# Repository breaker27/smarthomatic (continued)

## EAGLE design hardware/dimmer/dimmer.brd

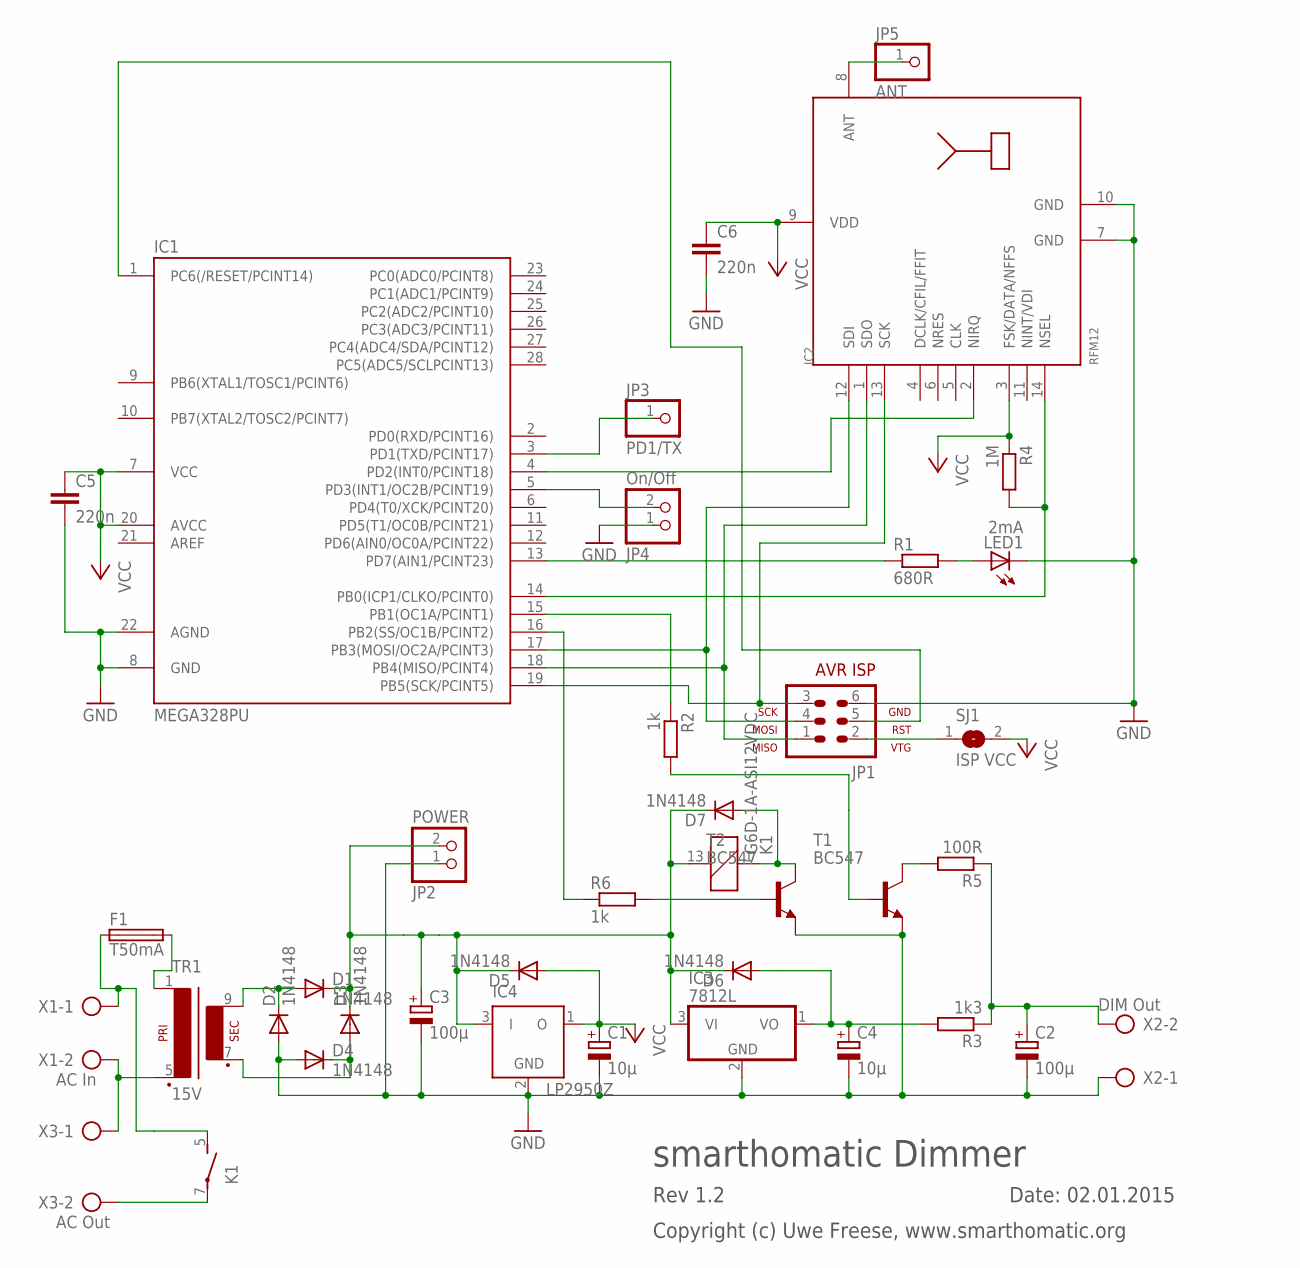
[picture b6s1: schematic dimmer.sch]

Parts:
C1, C4: 10µ; E1,8-4
C2, C3: 100µ; E1,8-4
C5, C6: 220n; C2.5-3
D1, D2, D3, D4, D5, D6, D7: 1N4148; DO35-7
F1: T50mA; SH22,5
IC1: MEGA328PU; DIL28-3
IC2: RFM12; RFM
IC3: 7812L; TO92
IC4: LP2950Z; TO92
JP1: AVR-ISP-6
JP2: POWER; 1X02
JP3: PD1/TX; 1X01
JP4: On/Off; 1X02
JP5: ANT; 1X01
K1: G6D-1A-ASI12VDC; G6D
LED1: 2mA; LED3MM
R1: 680R; 0207/7
R2, R6: 1k; 0207/7
R3: 1k3; 0207/7
R4: 1M; 0207/7
R5: 100R; 0207/7
SJ1: ISP VCC; SJ
T1, T2: BC547; TO92
TR1: 15V; EI30-1
X1: AC In; AK500/2
X2: DIM Out; AK500/2
X3: AC Out; AK500/2

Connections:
GND: C1.-, C2.-, C3.-, C4.-, C5.2, C6.2, D2.A, D4.A, IC1.8 (GND), IC1.22 (AGND), IC2.7 (GND), IC2.10 (GND), IC3.2 (GND), IC4.2 (GND), JP1.6, JP2.1, JP4.1, LED1.K (C), T1.1 (E), T2.1 (E), X2.1
unnamed: D1.A, D2.C, TR1.9 (S4)
unnamed: R5.2, T1.3 (C)
unnamed: IC1.17 (PB3(MOSI/OC2A/PCINT3)), IC2.12 (SDI), JP1.4
unnamed: IC1.18 (PB4(MISO/PCINT4)), IC2.1 (SDO), JP1.1
unnamed: IC1.19 (PB5(SCK/PCINT5)), IC2.13 (SCK), JP1.3
unnamed: IC1.13 (PD7(AIN1/PCINT23)), R1.1
unnamed: D3.A, D4.C, TR1.7 (S3)
unnamed: IC1.1 (PC6(/RESET/PCINT14)), JP1.5
unnamed: C3.+, D1.C, D3.C, D5.C, D6.C, D7.C, IC3.3 (VI), IC4.3 (I), JP2.2, K1.13 (2)
unnamed: C4.+, D6.A, IC3.1 (VO), R3.2
unnamed: IC2.8 (ANT), JP5.1
unnamed: LED1.A, R1.2
unnamed: IC1.14 (PB0(ICP1/CLKO/PCINT0)), IC2.14 (NSEL), R4.2
unnamed: IC1.15 (PB1(OC1A/PCINT1)), R2.1
unnamed: IC1.4 (PD2(INT0/PCINT18)), IC2.2 (NIRQ)
unnamed: R2.2, T1.2 (B)
unnamed: C2.+, R3.1, R5.1, X2.2
unnamed: D7.A, K1.1, T2.3 (C)
unnamed: TR1.5 (P2), X1.2, X3.1
unnamed: K1.7, X3.2
unnamed: JP1.2, SJ1.1
unnamed: F1.1, K1.5 (S), X1.1
unnamed: F1.2, TR1.1
unnamed: R6.2, T2.2 (B)
unnamed: IC1.16 (PB2(SS/OC1B/PCINT2)), R6.1
unnamed: IC1.3 (PD1(TXD/PCINT17)), JP3.1
unnamed: IC1.5 (PD3(INT1/OC2B/PCINT19)), JP4.2

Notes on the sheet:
smarthomatic Dimmer
Date: 02.01.2015
Rev 1.2
Copyright (c) Uwe Freese, www.smarthomatic.org

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
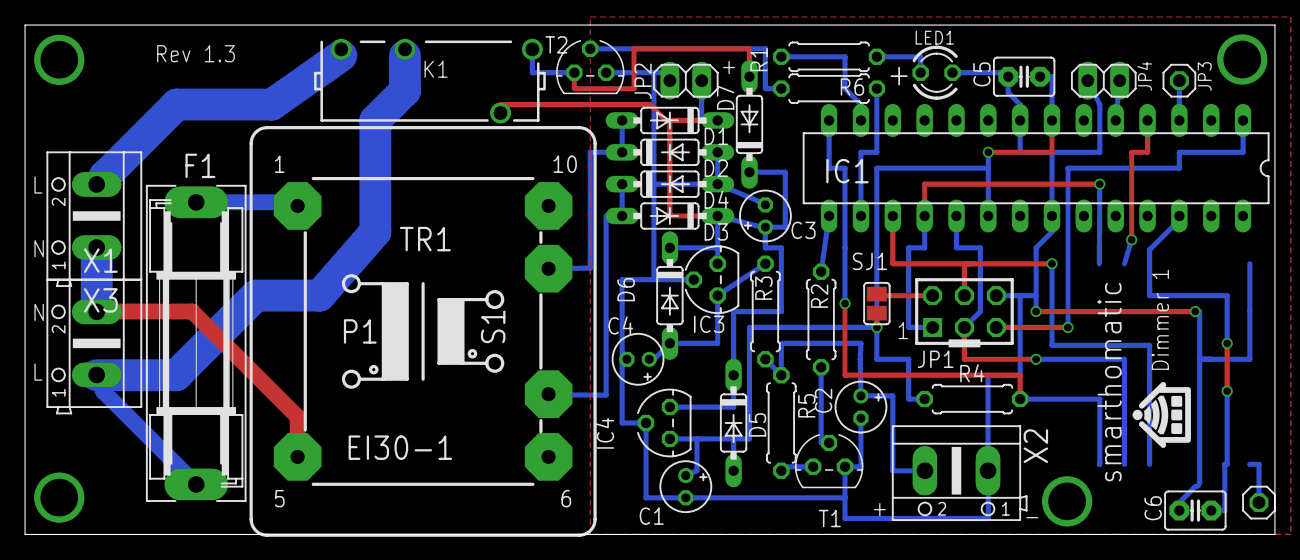
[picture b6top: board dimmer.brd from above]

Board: 2 copper layers, 99.7 x 40.6 mm, 38 parts (1 on the bottom side), 30 nets.

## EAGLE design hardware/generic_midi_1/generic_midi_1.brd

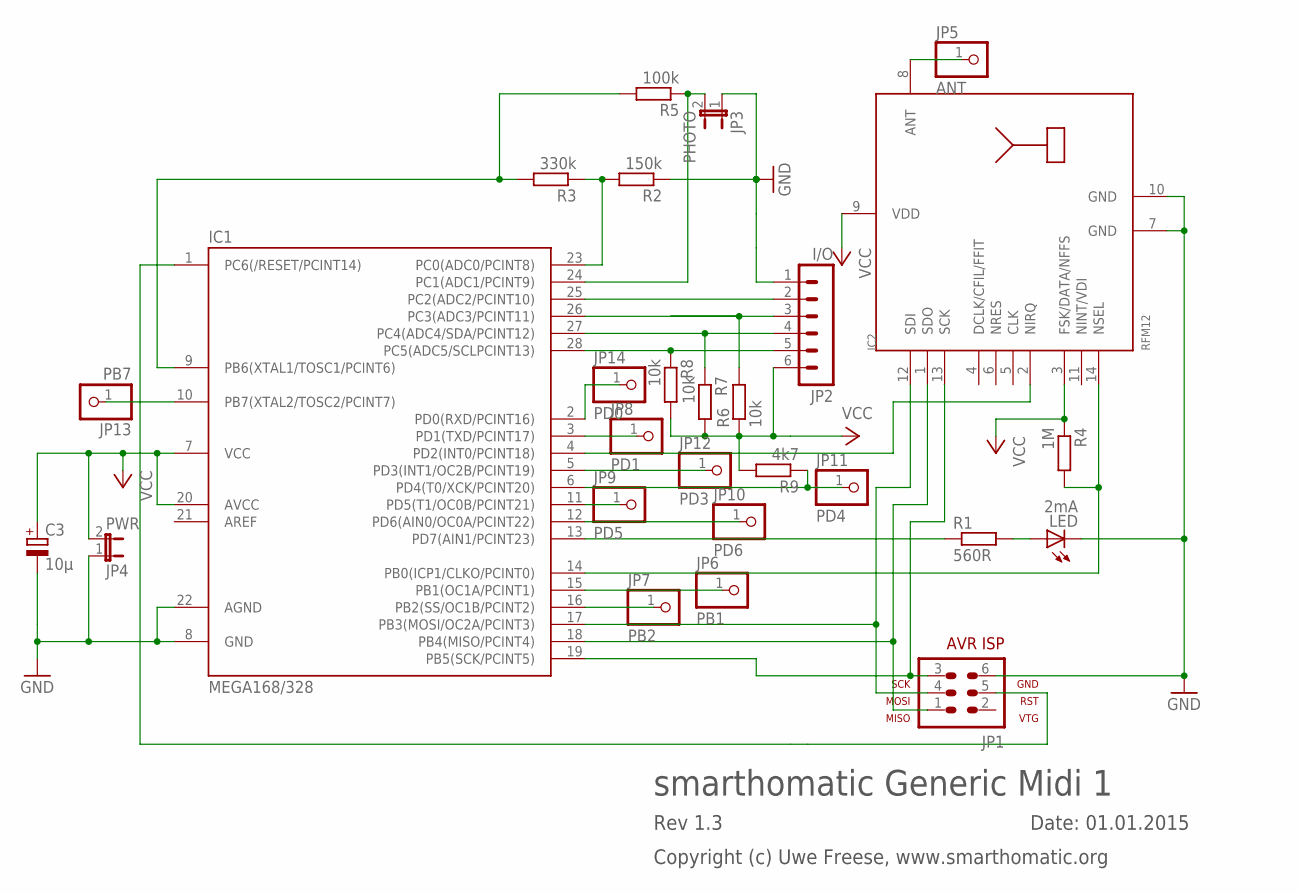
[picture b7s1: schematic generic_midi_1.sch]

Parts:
C3: 10µ; E1,8-4
IC1: MEGA168/328; DIL28-3
IC2: RFM12; RFM
JP1: AVR-ISP-6
JP2: I/O; MA06-1
JP3: PHOTO; JP1
JP4: PWR; JP1
JP5: ANT; 1X01
JP6: PB1; 1X01
JP7: PB2; 1X01
JP8: PD1; 1X01
JP9: PD5; 1X01
JP10: PD6; 1X01
JP11: PD4; 1X01
JP12: PD3; 1X01
JP13: PB7; 1X01
JP14: PD0; 1X01
LED: 2mA; LED3MM
R1: 560R; 0207/7
R2: 150k; 0207/7
R3: 330k; 0207/7
R4: 1M; 0207/7
R5: 100k; 0207/7
R6, R7, R8: 10k; 0207/7
R9: 4k7; 0207/7

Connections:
GND: C3.-, IC1.8 (GND), IC1.22 (AGND), IC2.7 (GND), IC2.10 (GND), JP1.6, JP2.1, JP3.1, JP4.1, LED.K (C), R2.1
unnamed: IC1.24 (PC1(ADC1/PCINT9)), JP3.2, R5.1
unnamed: IC1.17 (PB3(MOSI/OC2A/PCINT3)), IC2.12 (SDI), JP1.4
unnamed: IC1.18 (PB4(MISO/PCINT4)), IC2.1 (SDO), JP1.1
unnamed: IC1.19 (PB5(SCK/PCINT5)), IC2.13 (SCK), JP1.3
unnamed: IC1.13 (PD7(AIN1/PCINT23)), R1.1
unnamed: IC1.27 (PC4(ADC4/SDA/PCINT12)), JP2.4, R7.1
unnamed: IC1.1 (PC6(/RESET/PCINT14)), JP1.5
unnamed: IC1.28 (PC5(ADC5/SCLPCINT13)), JP2.5, R8.1
unnamed: IC1.26 (PC3(ADC3/PCINT11)), JP2.3, R6.2
unnamed: IC2.8 (ANT), JP5.1
unnamed: LED.A, R1.2
unnamed: IC1.14 (PB0(ICP1/CLKO/PCINT0)), IC2.14 (NSEL), R4.2
unnamed: IC1.11 (PD5(T1/OC0B/PCINT21)), JP9.1
unnamed: IC1.4 (PD2(INT0/PCINT18)), IC2.2 (NIRQ)
unnamed: IC1.12 (PD6(AIN0/OC0A/PCINT22)), JP10.1
unnamed: IC1.15 (PB1(OC1A/PCINT1)), JP6.1
unnamed 18: IC1.23 (PC0(ADC0/PCINT8)), R2.2, R3.1; also elsewhere on the board
unnamed: IC1.16 (PB2(SS/OC1B/PCINT2)), JP7.1
unnamed: IC1.3 (PD1(TXD/PCINT17)), JP8.1
unnamed: IC1.25 (PC2(ADC2/PCINT10)), JP2.2
unnamed: IC1.6 (PD4(T0/XCK/PCINT20)), JP11.1, R9.1
unnamed: IC1.5 (PD3(INT1/OC2B/PCINT19)), JP12.1
unnamed: IC1.9 (PB6(XTAL1/TOSC1/PCINT6)), R3.2, R5.2
unnamed: IC1.10 (PB7(XTAL2/TOSC2/PCINT7)), JP13.1
unnamed: IC1.2 (PD0(RXD/PCINT16)), JP14.1
unnamed 27: JP1.2; also elsewhere on the board
VCC: C3.+, IC1.7 (VCC), IC1.20 (AVCC), IC2.3 (FSK/DATA/NFFS), IC2.9 (VDD), JP2.6, JP4.2, R4.1, R6.1, R7.2, R8.2, R9.2; also elsewhere on the board

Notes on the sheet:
smarthomatic Generic Midi 1
Date: 01.01.2015
Rev 1.3
Copyright (c) Uwe Freese, www.smarthomatic.org

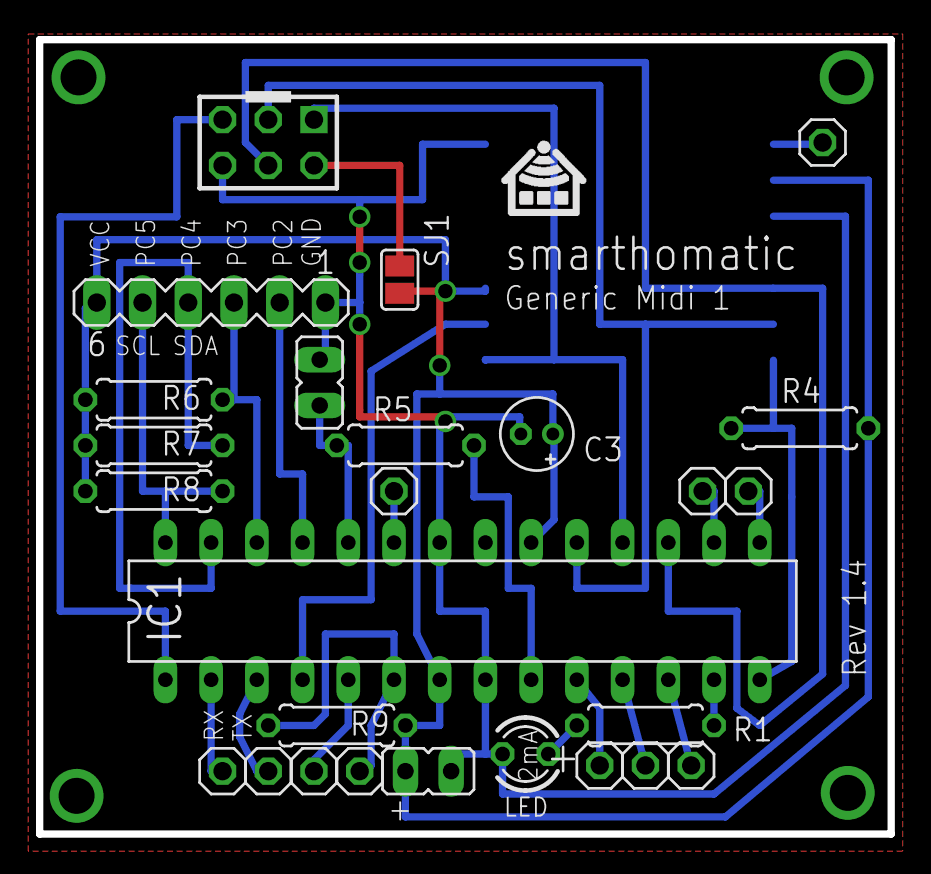
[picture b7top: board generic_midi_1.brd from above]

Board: 2 copper layers, 47.3 x 44.1 mm, 27 parts (1 on the bottom side), 28 nets.

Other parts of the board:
JP15: PC0; 1X01
SJ1: VCC; SJ

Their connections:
unnamed 18: JP15.1; also elsewhere on the board
unnamed 27: SJ1.1; also elsewhere on the board
VCC: SJ1.2; also elsewhere on the board

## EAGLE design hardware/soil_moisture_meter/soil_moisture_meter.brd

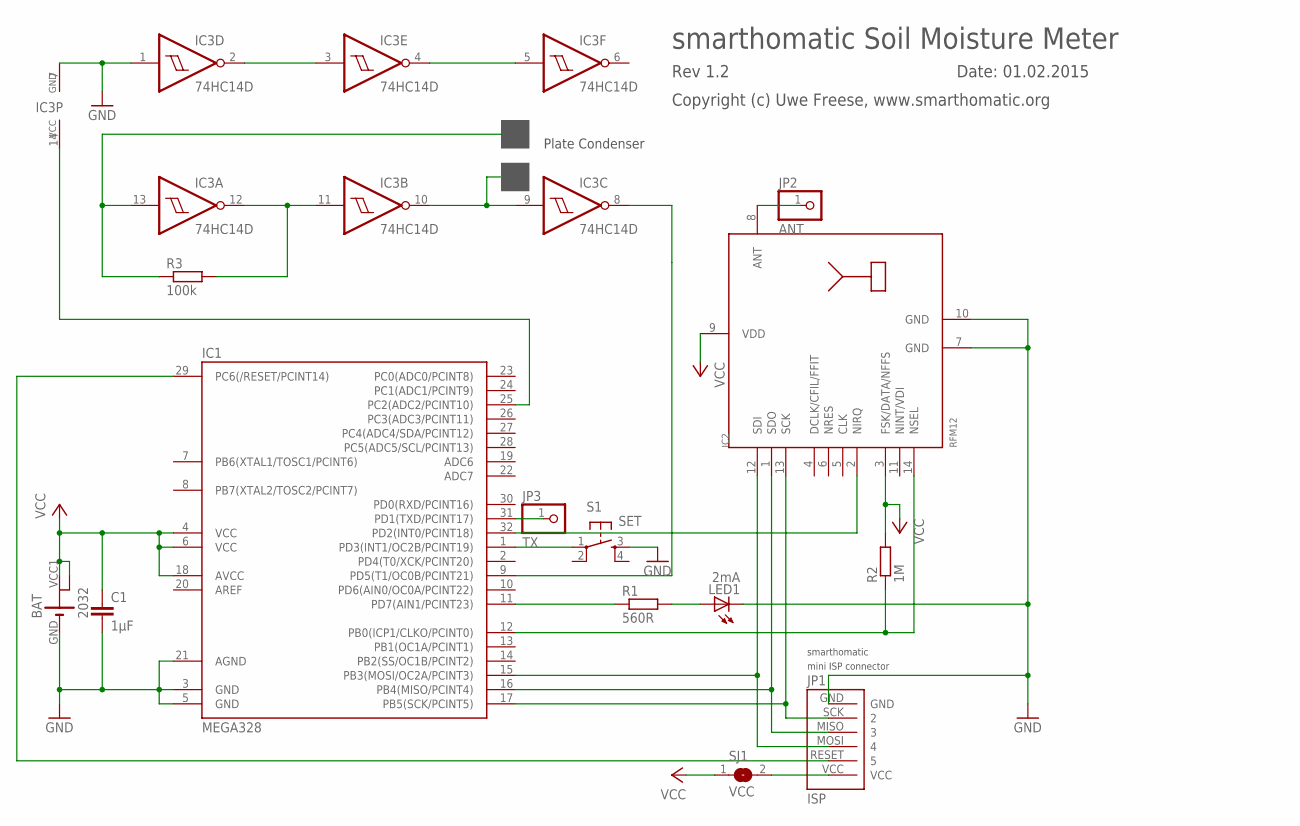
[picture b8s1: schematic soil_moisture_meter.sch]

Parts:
BAT: 2032; KZH20SMD
C1: 1µF; C0603
IC1: MEGA328; TQFP32-08
IC2: RFM12; RFM
IC3: 74HC14D; SO14
JP1: ISP; PINHD_1X6_1.27
JP2: ANT; 1X01
JP3: TX; 1X01
LED1: 2mA; LED3MM
R1: 560R; R0603
R2: 1M; R0603
R3: 100k; R0603
S1: SET; SCHURTER_LSG
SJ1: VCC; SJ

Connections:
GND: BAT.GND, C1.2, IC1.3 (GND), IC1.5 (GND), IC1.21 (AGND), IC2.7 (GND), IC2.10 (GND), IC3.1 (I), IC3.7 (GND), JP1.GND, LED1.K (C), S1.3 (S)
unnamed: JP1.VCC, SJ1.2
unnamed: IC3.11 (I), IC3.12 (O), R3.2
unnamed: IC1.15 (PB3(MOSI/OC2A/PCINT3)), IC2.12 (SDI), JP1.MOSI (4)
unnamed: IC1.16 (PB4(MISO/PCINT4)), IC2.1 (SDO), JP1.MISO (3)
unnamed: IC1.17 (PB5(SCK/PCINT5)), IC2.13 (SCK), JP1.SCK (2)
unnamed: IC1.11 (PD7(AIN1/PCINT23)), R1.1
unnamed: IC3.9 (I), IC3.10 (O)
unnamed: IC1.29 (PC6(/RESET/PCINT14)), JP1.RESET (5)
unnamed: IC3.13 (I), R3.1
unnamed: IC1.9 (PD5(T1/OC0B/PCINT21)), IC3.8 (O)
unnamed: LED1.A, R1.2
unnamed: IC1.12 (PB0(ICP1/CLKO/PCINT0)), IC2.14 (NSEL), R2.1
unnamed: IC1.32 (PD2(INT0/PCINT18)), IC2.2 (NIRQ)
unnamed: IC2.8 (ANT), JP2.1
unnamed: IC3.4 (O), IC3.5 (I)
unnamed: IC3.2 (O), IC3.3 (I)
unnamed: IC1.1 (PD3(INT1/OC2B/PCINT19)), S1.1
unnamed: IC1.25 (PC2(ADC2/PCINT10)), IC3.14 (VCC)
unnamed: IC1.31 (PD1(TXD/PCINT17)), JP3.1
VCC: BAT.VCC1, BAT.VCC2, C1.1, IC1.4 (VCC), IC1.6 (VCC), IC1.18 (AVCC), IC2.3 (FSK/DATA/NFFS), IC2.9 (VDD), R2.2, SJ1.1

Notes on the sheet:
smarthomatic Soil Moisture Meter
Date: 01.02.2015
Rev 1.2
Copyright (c) Uwe Freese, www.smarthomatic.org
Plate Condenser

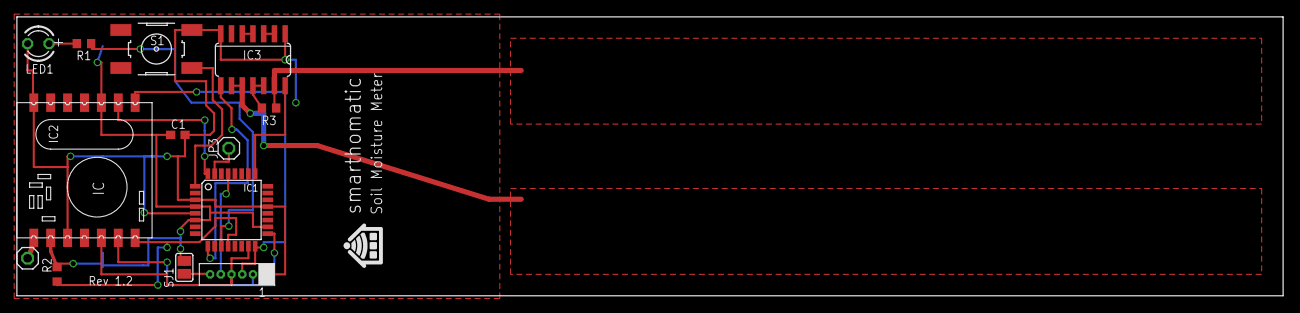
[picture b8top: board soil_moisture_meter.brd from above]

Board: 2 copper layers, 149.9 x 33.0 mm, 14 parts (1 on the bottom side), 21 nets.

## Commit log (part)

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2014-09-15 Use a (fixed) exponential (-like) PWM lookup table to make the brightness levels appear linear.
2014-09-16 Update comment. Remove brightness translation table because a fixed lookup table is implemented to make the brightness levels appear linear to the human eye.
2014-09-18 AVR Crypto Library added
2014-09-20 backport SVN commit ID from fhem repo
2014-09-20 Add soil moisture meter firmware (first version - does not measure anything).
2014-09-21 Add soil moisture meter hardware layout + schematics.
2014-09-21 Add humidity message.
2014-09-22 Change GPIO message format.
2014-09-27 Enter initialization after long button press. Remember dry threshold after averaging some values. Support averaging intervals and wakeup times from e2p config. Send battery status after given amount 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
2014-09-27 Mark messages as deprecated.
2014-09-28 AVR Crypto-Lib added
2014-10-03 Correct cyclic sending of battery status. Add debug function for raw value. Move MIN function to util_generic.h.
2014-10-03 Add default e2p file.
2014-10-03 Check relais number to switch and ignore call when number higher than relais count.
2014-10-03 At power on, show colors shortly to tell user that power is connected (status LED may not be visible).
2014-10-04 fhem: added support to set DigitalPins and DigitalPorts
    also DigitalPinTimeout and DigitalPortTimeout
2014-10-04 fhem: update documentation
2014-10-04 Change back battery measuring interval to correct value.
2014-10-09 Correct message names.
2014-10-09 Correct using the right message ID (DigitalPort instead of DigitalPin).
2014-10-09 Exclude BOD disable in sleep for ATMega329 which does not support it.
2014-10-14 Add test case.
2014-10-25 Fix: Reset measurement counter after sending DigitalPort message.
2014-11-16 Allow multiple enum definitions in e2p and packet definition files as long as they are identical. Implement "DeviceInfo" message which includes DeviceType and version info and mark old "Version" mess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
2014-12-14 Add support for humidity sensor HTU21d
2015-01-01 Add pull-up resistor for possible one-wire sensor on PD4.
2015-01-02 Change SMD solder pad.
2015-01-04 Support HTU21D temperature/humidity sensor (I2C).
2015-01-04 Rename functions from "...version..." to "...deviceinfo..." according to the message name.
2015-01-04 Send error Ack when MessageID is not supported. This is to reduce traffic (and react according spec). Without this function, the e.g. BaseStation would retry the "Set" request and produce more traffi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
2015-01-10 Change default values for SoilMoistureMeter.
2015-01-11 Updated header files with corrected wake-up values.
2015-02-01 Change mini ISP connector and add 6th pin for VCC. Add solder jumper for VCC. Move ANT pin near RFM12B module. Remove resistor between 74GC14D and ATMega. Change LED resistor value.
2015-02-07 Fix calculation of negative temperatures with DS18B20 sensor.
2015-02-13 disable COM0A1 and COM0B1 when value is 0
2015-02-14 add brightness slider to fhem for rgbdimmer
2015-02-15 Set DevStateIcon for SoilMoistureMeter.
2015-02-21 Fix writing timeout value of 0 to e2p when timeout was counted down completely. The power switch was toggling state again after timeout after power loss even if this was not intended. (Thanks to wurs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
2015-02-26 rgb dimmer: add default color to eeprom, load default color after startup
2015-02-28 envsensor: init i2c when only temperature is used
2015-03-01 Add SmoothingPercentage as e2p value. This is the size of a moving window in which the absolute humidity (0 to 100 percent) is smoothed. This is necessary because the raw values typically show some s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
2015-03-02 Send DeviceInfo and Battery status twice after start up (inserting battery). Minor code beautifications.
2015-03-02 Beautify code.
2015-03-07 Move LED blink functions. Speed up sending from queue to 0.25s. Remove debug code.
2015-03-07 Call rfm12_tick directly in send function. Reorder UART output. Time for sending packets (from reception of last character to rfm12_tick) is now down to 95ms with 19200 baud and 18ms with 115200 baud.
2015-03-07 Add CRC32 at the end of the packet data string. Abbreviate field names in the received packet that is printed on the serial line. This reduces the delay for transferring data from/to the server (e.g.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
2015-03-08 Add command to the base station where the user suffixes his input with a CRC32 (8 characters). If it doesn't match, the command is ignored. This is to be safe against interferences/problems on the se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
2015-03-08 Shorten debug output to speed up sending.
2015-03-08 Change test packets to new format.
2015-03-08 Correct regular expressions and dispose "PKT:SID=0;" strings (which are from the messages originally sent by FHEM itself).
2015-04-13 Add solder jumper to PCB for ISP VCC pin.
2015-05-01 Sleep for 250 milliseconds after sending a string over UART to the base station to make sure it can process the command before the next is sent.
2015-05-17 Hotfix for buggy CRC check with GCC 4.7.2 on linux.
2015-05-23 Implement watchdog function to reset RFM12B when nothing is received some time.
2015-06-06 Switch RFM interrupt off and on in reset function.
2015-06-21 Add HardwareError message to FHEM parser.
2015-06-21 Fix variable access.
2015-06-21 Update description of TransceiverWatchdogTimeout value.
2015-09-27 Increase delay for reset / power down time.
2015-10-25 Update to latest SCH Develop
2015-10-27 Include additional files that are already used in project file.
2015-10-30 Make ATMega soft reset (instead of only RFM12 reset) when RFM12 hangs. Report different startup reasons in (updated) HardwareError message.
2015-10-30 Updated dimmer hardware to V1.3, where RFM12 power is connected to an ATMega I/O pin to restart it if necessary using the transceiver watchdog functionality.
2015-11-15 Update images of PCB V1.1.
2016-04-03 Support ATMega324PA in makefile, used for tea maker.
2016-04-10 Add source code for tea maker.
2016-04-10 Add TeaMaker device with ID 90.
2016-04-16 Read preset from e2p.
2016-04-22 Clean up imports.
2016-04-22 Add possibility to switch byte array editor to string mode (instead of hex mode). This can be used to easily define tea maker strings shown on the display.
2016-04-23 Add possibility to define microcontroller model in e2p layout file (used by e2p editor, which also calls the flash program).
2016-04-23 Add e2p_teamaker.h file to project.
2016-04-23 Use specified MicrocontrollerModel in e2p layout for calling the flash utility.
2016-07-24 Make winch (servo) work on target MC.
2017-10-10 Remove project file from autorouter.
2017-11-11 Generic Maxi Speed V1.2: Added transistor to switch power of RFM module to allow restart or module if transceiver doesn't react anymore.
2017-11-12 Improve comments in code.
2019-08-07 Use watchdog in devices that are in receive mode to detect hanging RFM12 module. Reset device in this case. The behaviour can be enabled in the E2P.
2019-08-08 PowerSwitch: Add E2P option for an optional manual switch.
2019-08-08 PowerSwitch: Read new switch mode from e2p.
2019-08-09 Reorder switch modes as they are in a more consistent order.
2019-08-10 Remove WinAVR files from gitignore, since these were removed from the repo already.
2019-10-20 Update copyright info.
2019-11-10 Raise RFM12_TX_BUFFER_SIZE and RFM12_RX_BUFFER_SIZE from 50 to 64 bytes for all devices, because it is now necessary for the ParticulateMatter message (> 32 bytes).
2019-11-11 Add e2p configuration for ParticulateMatter sensor.
2019-11-11 Add messages and e2p functions for ParticulateMatter sensor in source code.
2019-11-16 Add support of SPS30 sensor to envsensor.
2019-11-16 Support new FloatValue type in FHEM implementation.
2019-11-16 Fix makefile to consider sps30.
2019-11-17 Envsensor: Add PowerPinMode e2p config option. This allows to switch the power pin explicitly on before i2c measurement for sensors that need the 5V step-up converter. Before, it was implicitly switc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
2020-06-14 Maybe multiple packets need to be sent
    If the wakeup count for different measurements is reached at the same time, only one of them gets sent. F.ex. if you check the temperature every 15 minutes, and the brightness every hour, at the four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
    Is this by purpose, to prevent the envsensor from sending too much packets?
2022-09-19 Implemented switch on/off delay. When set in e2p, a status change of the optional switch is considered to calculate the relais state only after the defined delay.
2022-09-21 Update FHEM module for smarthomatic. Update default baudrate of base station to 115200. Update description.
2022-09-23 Correct that only 2 relais states are set (only 8 bit available).
2022-09-25 Fix calculation of battery percentage.
2022-09-25 Remove unused variable.
2022-10-03 Update spaces in PowerSwitch Makefile.
2022-10-03 Set status "released" for some of the messages in the message catalog.
2022-10-04 Introducing "Deliver" message type for sending a status with request for an acknowledge.
2022-11-24 Add placing and schematic images.
2023-01-26 Support atmega644p in Makefile.
2023-01-27 Remove trailing spaces.
2023-01-28 Initial files to move RGB LED code to common source files, since the functionality shall be used by the controller as well.
2023-01-29 HW Break! Switch pins for Blue LED and Speaker on RGB Dimmer, so that Blue LED is on PD3 and uses timer 2 (8 Bit) and Speaker can now use PB1 and use 16 Bit timer 1. The higher accuracy timer is bett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
2023-01-31 Define new messages for Controller and RGB Dimmer device.
2023-02-03 Correct timer divider.
2023-02-03 Add melody test (debug) function.
2023-02-05 Use a more generic effect parameter instead of a "slide" parameter for the melody.
2023-02-06 Implement "Tone" and "Melody" functions from "Audio" message group for FHEM.
2023-02-28 Limit effect to 1 since others are not implemented yet.
2023-03-05 Clean UART output earlier to clean up the send buffer. Otherwise it overflows when using large (64 byte) packets.
2023-03-05 Initialize variables to avoid compiler warning, even they are definitly not used uninitialized according the if-statements.
2023-03-06 Add shell script to start SHC_parser_test.
2023-03-10 Implement generation of ByteArray access functions in the E2P Editor's SourceCodeGenerator.
2023-03-10 Update fuses for controller.
2023-03-10 Correct pin numbers used for RFM12 in controller.
2023-03-12 Change "Text" message format so the text bytes are aligned. Saving one bit doesn't make the messages smaller.
2023-03-12 Add FHEM SHC parser test case for controller device.
2023-03-12 Implement to correctly receive Display-Text function in controller.
2023-04-11 Controller update: Support LCD. Support menu with user options. Support buttons to select menu items.
2023-04-11 Add sound (key tone) option for controller in e2p.
2023-04-11 Implement automatic jump back to first LCD page after timeout. Send menu selection via SHC message incl. retries. Reaction on delivery ack is not implemented yet.
2023-04-13 Support Deliver Ack in basestation.
2023-04-13 Fix basestation e2p layout. Add UartBaudRate again.
2023-04-16 Add rfm12_tx_status function to allow detecting if a packet in the buffer is completely sent.
2023-04-16 Call new rfm12_send_wait_led function immediately when packets shall be sent. Use new rfm12_delay20 function and therefore speed up sending packets.
2023-04-16 Align UART output format.
2023-04-16 Fix that the last character in the line can be displayed.
2023-04-18 Allow to configure in e2p the text shown when sending the menu options. Reorder an e2p value.
2023-04-20 Extend max. virtual pages to 4.
2023-04-25 Support up to 32 lines in the text message of the virtual display (= 8 pages).
2023-05-09 Support display_backlight function in controller device.
2023-05-11 Support ATMega1284 in E2P editor.
2023-05-16 Fix: Clear the correct virtual LCD page when leaving the menu.
2023-05-16 FHEM: Use "Set" instead of "SetGet" when sending Controller-Text message. This reduces the size of the answer from the controller.
2023-05-19 Switch off UART debugging.
2023-05-25 Define to not send menu selection without user interaction by default. This can lead to unwanted behaviour in receiving home automation software as it looks as if the user selected something.
2023-05-29 When a menu selection is "delivered" by a controller to FHEM, then set additionally the reading menuSelectionDelivery to distinguish this compared to a menu selection change initiated by a FHEM "set"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
